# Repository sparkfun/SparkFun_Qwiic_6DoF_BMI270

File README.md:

SparkFun Qwiic 6DoF BMI270
========================================

<table class="table table-hover table-striped table-bordered">
    <tr align="center">
        <td></td>
        <td></td>
    </tr>
    <tr align="center">
        <td><i><a href="https://www.sparkfun.com/products/22397">SparkFun 6DoF IMU Breakout - BMI270 (Qwiic)</a></td></i></td>
        <td><i><a href="https://www.sparkfun.com/products/22398">SparkFun Micro 6DoF IMU Breakout - BMI270 (Qwiic)</a></i></td>
    </tr>
</table>

The SparkFun BMI270 6DoF IMU Breakout is a Qwiic-enabled breakout board based on the ultra-low power BMI270 from Bosch. This chip is a highly integrated, low power IMU optimized for wearables providing precise acceleration, angular rate measurement and intelligent on-chip motion-triggered interrupt features.. Not only does the BMI270 comprise a fast and sensitive accelerometer and gyro pair, but it also contains a number of intelligent, on-chip motion-triggered interrupt features.  

Our Standard-sized 1in. x 1in. Qwiic BMI270 IMU Breakout makes it easy to add this sensor to your project using our solderless Qwiic cables and compatible controllers. If you still prefer to use a breadboard, don't worry, we've still broken out all IO pins to 0.1" spaced pin-headers along the sides of the board. On-board solder jumpers allow you to easily select the device address, remove the I²C pull-ups, and disable the power LED if need be. 

Our Micro-sized 0.3in. x 0.75in. footprint makes this breakout board an ideal option for your smallest projects using our solderless Qwiic cables and compatible controllers. On-board solder jumpers allow you to easily select the device address, remove the I²C pull-ups, and disable the power LED if need be. 

The 6-axis sensor combines a 16-bit tri-axial gyroscope and a 16-bit tri-axial accelerometer featuring Bosch’s automotive-proven gyroscope technology. BMI270 includes several functionalities such as an integrated plug-and-play step counter/detector and gesture detection for wrist-worn devices. Moreover, the IMU is suitable for hearables, smart clothes, smart shoes, smart glasses and ankle bands.

Repository Contents
-------------------

* **/Documentation** - Data sheets, additional product information
* **/Hardware** - Eagle design files (.brd, .sch)
* **/Production** - Production panel files (.brd)

Documentation
--------------
* **[Library](https://github.com/sparkfun/SparkFun_BMI270_Arduino_Library)** - Arduino library for the SparkFun 6DoF IMU Breakout - BMI270 (Qwiic) and SparkFun Micro 6DoF IMU Breakout - BMI270 (Qwiic).
* **[Hookup Guide](http://docs.sparkfun.com/SparkFun_Qwiic_6DoF_BMI270/)** - Basic hookup guide for the SparkFun 6DoF IMU Breakout - BMI270 (Qwiic) and SparkFun Micro 6DoF IMU Breakout - BMI270 (Qwiic). 

License Information
-------------------

This product is _**open source**_! 

Please review the LICENSE.md file for license information. 

If you have any questions or concerns on licensing, please contact technical support on our [SparkFun forums](https://forum.sparkfun.com/viewforum.php?f=152).

Distributed as-is; no warranty is given.

- Your friends at SparkFun.

_<COLLABORATION CREDIT>_

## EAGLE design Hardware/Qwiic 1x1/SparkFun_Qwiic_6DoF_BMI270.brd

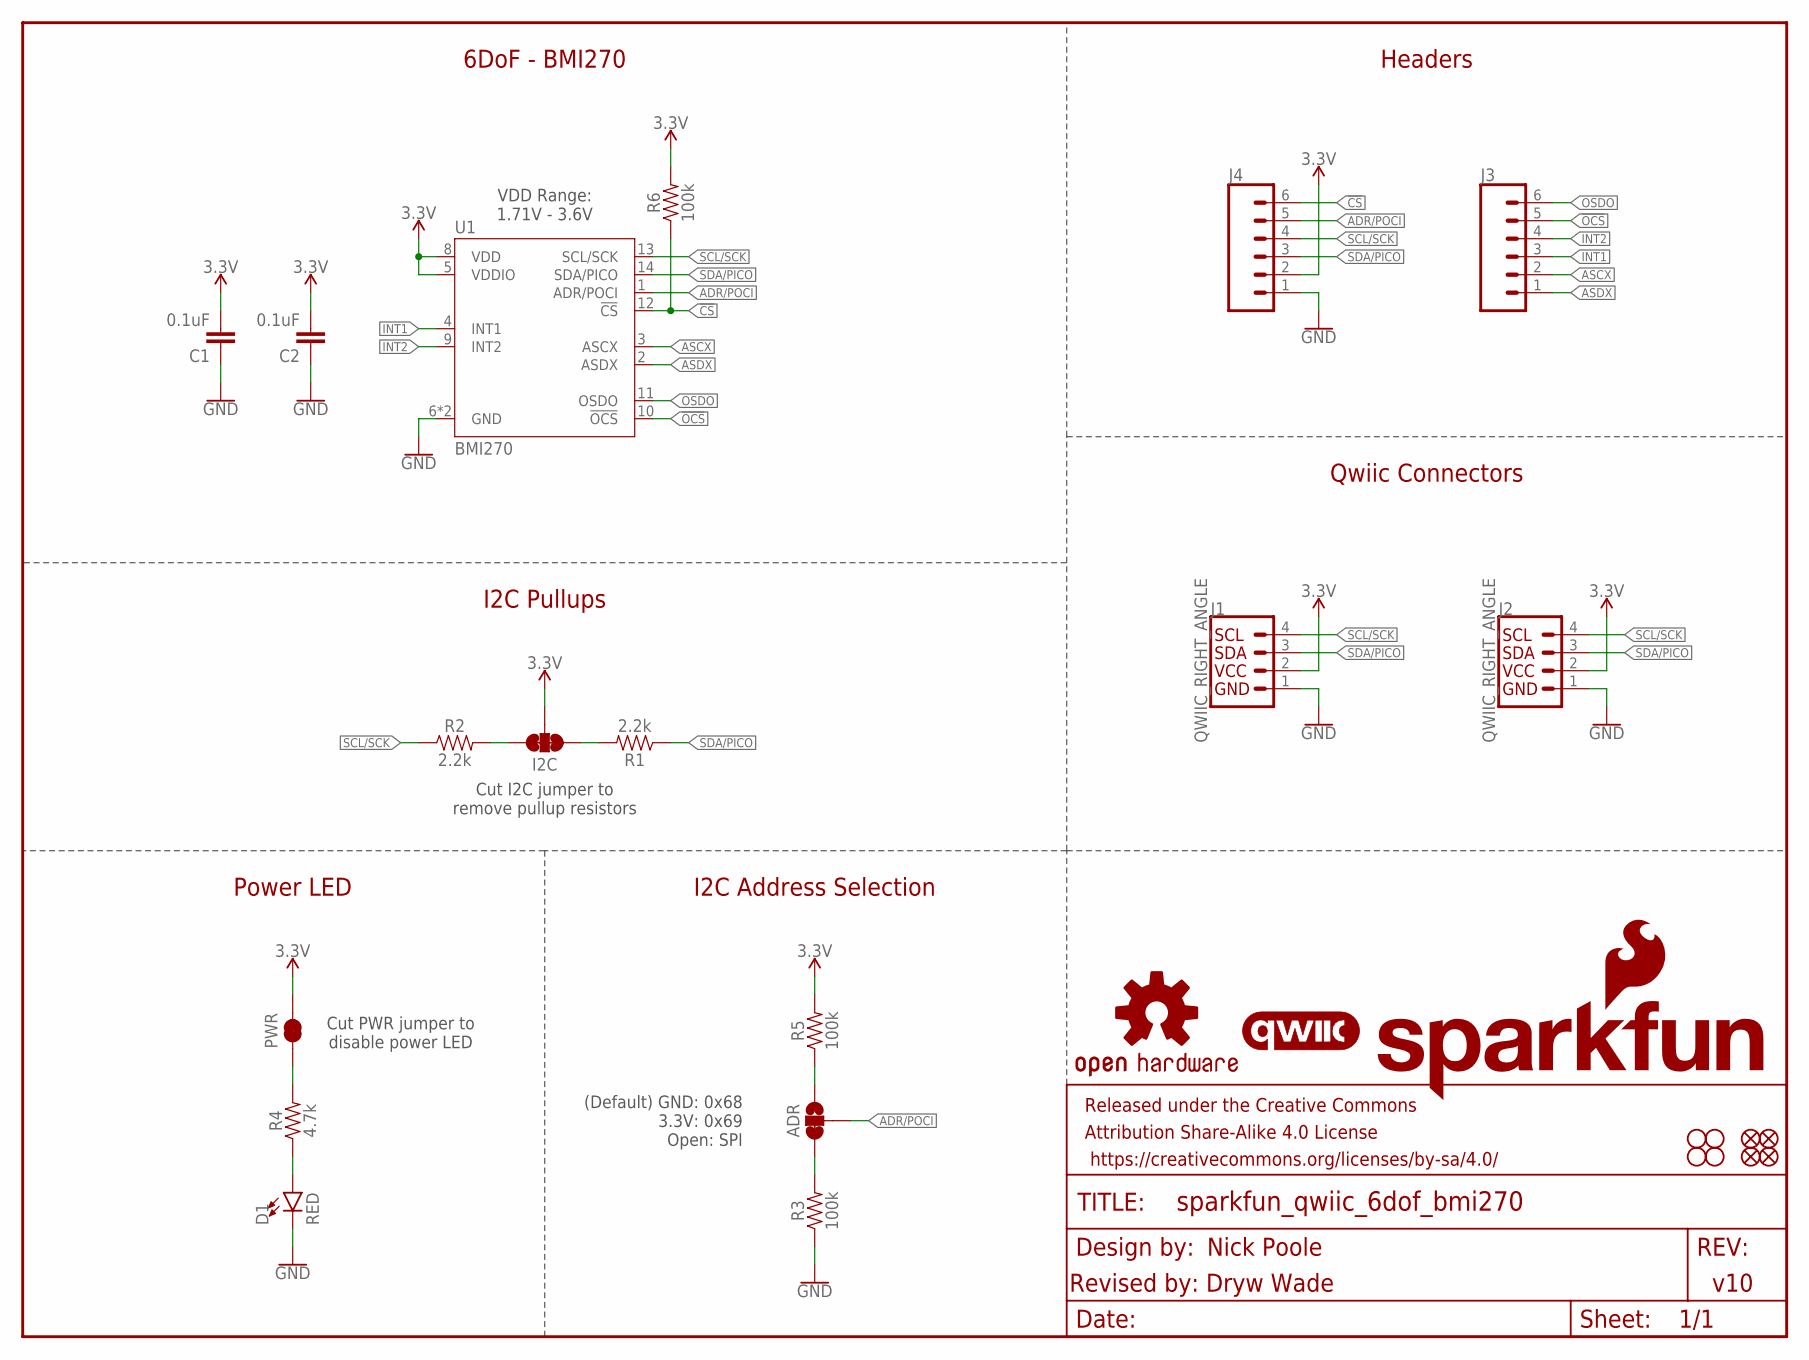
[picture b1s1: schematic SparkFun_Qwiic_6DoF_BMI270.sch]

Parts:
ADR: JUMPER-SMT_3_1-NC_TRACE_SILK; SMT-JUMPER_3_1-NC_TRACE_SILK
C1, C2: 0.1uF; 0603
D1: RED; LED-0603
FD1, FD2, FD3, FD4: FIDUCIAL1X2; FIDUCIAL-1X2
FRAME1: FRAME-LETTER; CREATIVE_COMMONS
H1, H2, H3, H4: STAND-OFF
I2C: JUMPER-SMT_3_2-NC_TRACE_SILK; SMT-JUMPER_3_2-NC_TRACE_SILK
J1, J2: QWIIC_RIGHT_ANGLE; JST04_1MM_RA
J3, J4: CONN_06NO_SILK_FEMALE_PTH; 1X06_NO_SILK
LOGO1: SFE_LOGO_NAME_FLAME.1_INCH; SFE_LOGO_NAME_FLAME_.1
LOGO2: QWIIC_LOGO_5MM; QWIIC_5MM
LOGO3: OSHW-LOGOS; OSHW-LOGO-S
PWR: JUMPER-SMT_2_NC_TRACE_SILK; SMT-JUMPER_2_NC_TRACE_SILK
R1, R2: 2.2k; 0603
R3, R5, R6: 100k; 0603
R4: 4.7k; 0603
U1: BMI270

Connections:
3.3V: C1.2, C2.2, I2C.2, J1.2, J2.2, J4.2, PWR.2, R5.2, R6.2, U1.5 (VDDIO), U1.8 (VDD)
!CS!: J4.6, R6.1, U1.12 (!CS!)
!OCS!: J3.5, U1.10 (!OCS!)
ADR/POCI: ADR.2, J4.5, U1.1 (ADR/POCI)
ASCX: J3.2, U1.3 (ASCX)
ASDX: J3.1, U1.2 (ASDX)
GND: C1.1, C2.1, D1.C, J1.1, J2.1, J4.1, R3.1, U1.6 (GND), U1.7 (GND)
INT1: J3.3, U1.4 (INT1)
INT2: J3.4, U1.9 (INT2)
unnamed: I2C.1, R1.2
unnamed: I2C.3, R2.2
unnamed: PWR.1, R4.2
unnamed: D1.A, R4.1
unnamed: ADR.1, R5.1
unnamed: ADR.3, R3.2
OSDO: J3.6, U1.11 (OSDO)
SCL/SCK: J1.4, J2.4, J4.4, R2.1, U1.13 (SCL/SCK)
SDA/PICO: J1.3, J2.3, J4.3, R1.1, U1.14 (SDA/PICO)

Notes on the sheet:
(Default) GND: 0x68 3.3V: 0x69 Open: SPI
Cut PWR jumper to disable power LED
Power LED
Headers
Qwiic Connectors
Nick Poole
Revised by: Dryw Wade
v10
6DoF - BMI270
Cut I2C jumper to remove pullup resistors
VDD Range: 1.71V - 3.6V
I2C Address Selection
I2C Pullups

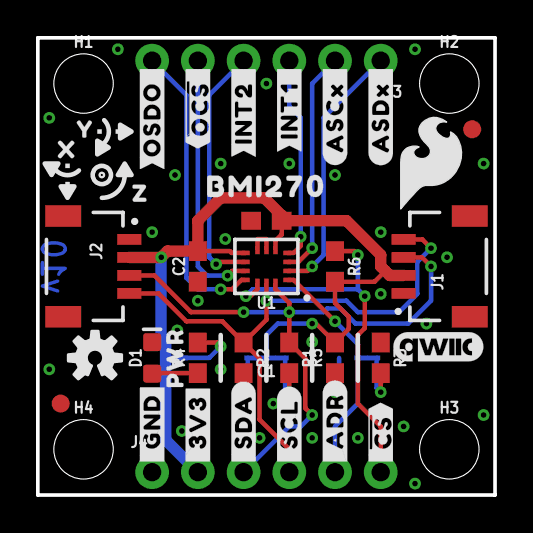
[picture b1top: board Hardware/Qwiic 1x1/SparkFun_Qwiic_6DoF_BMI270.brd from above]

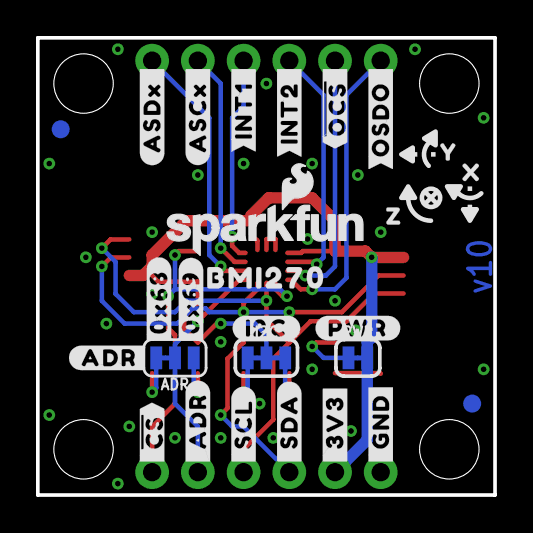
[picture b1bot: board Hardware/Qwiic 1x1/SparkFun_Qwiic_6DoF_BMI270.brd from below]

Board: 2 copper layers, 25.4 x 25.4 mm, 69 parts (27 on the bottom side), 18 nets.

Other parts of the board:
U$1: #I2C#0
U$2, U$14: #_SDA#0
U$3: SFE_LOGO_FLAME_.2
U$4: #PWR#0
U$5: #ADR#0
U$6: #0X68#0
U$7, U$13: #_3V3#0
U$8, U$17: #_#CS##0
U$9, U$16: #_ADR#0
U$10, U$15: #_SCL#0
U$11, U$27: #ASDX_#0
U$12, U$19: #_GND#0
U$18: #0X69#0
U$20, U$21: BMI2700
U$22, U$28: #ASCX_#0
U$23, U$29: #INT1_#0
U$24, U$30: #INT2_#0
U$25, U$31: ##OCS#_#0
U$26, U$32: #OSDO_#0
U$33: ORDERING_INSTRUCTIONS
U$34: PWR0
U$79, U$88: X0
U$80, U$89: Y0
U$81, U$90: Z0

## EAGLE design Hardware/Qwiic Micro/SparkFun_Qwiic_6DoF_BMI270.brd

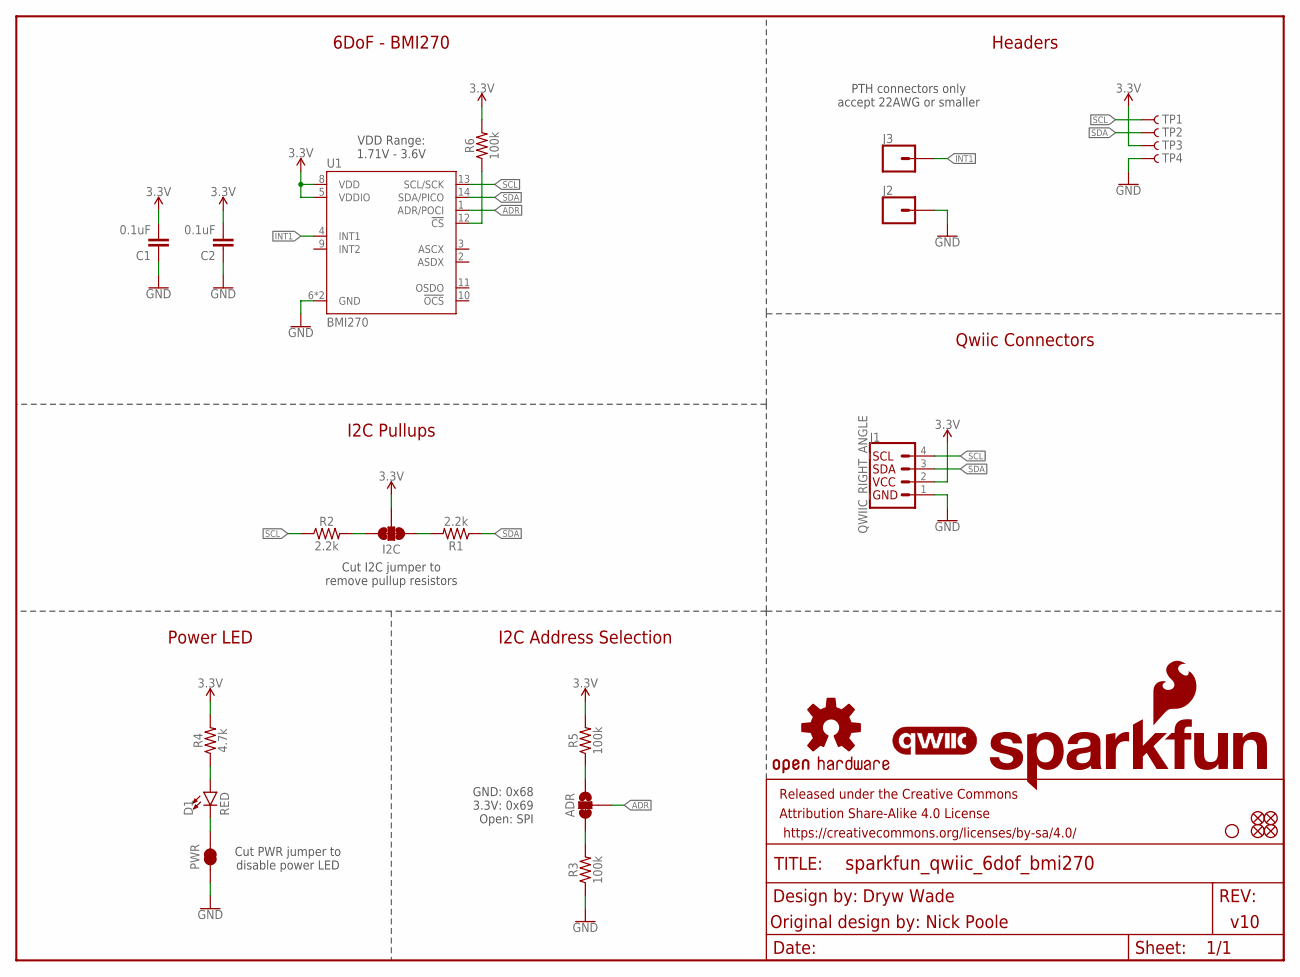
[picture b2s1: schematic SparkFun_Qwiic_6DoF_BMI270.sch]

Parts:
ADR: JUMPER-SMT_3_1-NC_TRACE_SILK; SMT-JUMPER_3_1-NC_TRACE_SILK
C1, C2: 0.1uF; 0402-TIGHT
D1: RED; LED-0402
FD1, FD2, FD3, FD4: FIDUCIALUFIDUCIAL; FIDUCIAL-MICRO
FRAME1: FRAME-LETTER; CREATIVE_COMMONS
H1: STAND-OFF
I2C: JUMPER-SMT_3_2-NC_TRACE_SILK; SMT-JUMPER_3_2-NC_TRACE_SILK
J1: QWIIC_RIGHT_ANGLE; JST04_1MM_RA
J2, J3: CONN_01_1MM; 1X01_1MM_NO_SILK
LOGO1: SFE_LOGO_NAME_FLAMEBLANK; BLANK
LOGO2: QWIIC_LOGO_3MM; QWIIC_3MM
LOGO3: OSHW-LOGOMINI; OSHW-LOGO-MINI
PWR: JUMPER-SMT_2_NC_TRACE_SILK; SMT-JUMPER_2_NC_TRACE_SILK
R1, R2: 2.2k; 0402-TIGHT
R3, R5, R6: 100k; 0402-TIGHT
R4: 4.7k; 0402-TIGHT
TP1, TP2, TP3, TP4: TEST-POINT3; PAD.03X.03
U1: BMI270

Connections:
3.3V: C1.2, C2.2, I2C.2, J1.2, R4.2, R5.2, R6.2, TP3.1, U1.5 (VDDIO), U1.8 (VDD)
ADR: ADR.2, U1.1 (ADR/POCI)
GND: C1.1, C2.1, J1.1, J2.1, PWR.1, R3.1, TP4.1, U1.6 (GND), U1.7 (GND)
INT1: J3.1, U1.4 (INT1)
unnamed: I2C.1, R1.2
unnamed: I2C.3, R2.2
unnamed: D1.C, PWR.2
unnamed: D1.A, R4.1
unnamed: ADR.1, R5.1
unnamed: ADR.3, R3.2
unnamed: R6.1, U1.12 (!CS!)
SCL: J1.4, R2.1, TP1.1, U1.13 (SCL/SCK)
SDA: J1.3, R1.1, TP2.1, U1.14 (SDA/PICO)

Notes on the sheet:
GND: 0x68 3.3V: 0x69 Open: SPI
Cut PWR jumper to disable power LED
Power LED
Headers
Qwiic Connectors
Dryw Wade
Original design by: Nick Poole
v10
6DoF - BMI270
Cut I2C jumper to remove pullup resistors
VDD Range: 1.71V - 3.6V
I2C Address Selection
I2C Pullups
PTH connectors only accept 22AWG or smaller

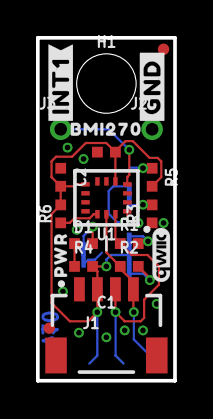
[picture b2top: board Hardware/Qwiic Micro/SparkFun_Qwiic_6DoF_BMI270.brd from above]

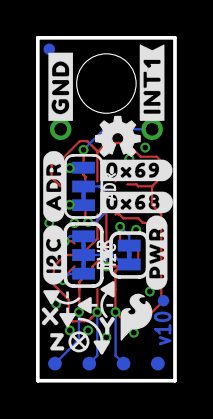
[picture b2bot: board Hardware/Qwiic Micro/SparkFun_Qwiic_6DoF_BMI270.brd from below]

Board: 2 copper layers, 7.6 x 19.1 mm, 45 parts (22 on the bottom side), 13 nets.

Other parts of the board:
U$1: #I2C#0
U$2, U$7: #GND#0
U$3: SFE_LOGO_FLAME_.1
U$4: #PWR#0
U$5: #ADR#0
U$6: #0X68#0
U$8, U$9: #INT1#0
U$18: #0X69#0
U$21: BMI2700
U$33: ORDERING_INSTRUCTIONS
U$34: PWR0
U$79: X0
U$80: Y0
U$81: Z0

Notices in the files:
parts and their libraries:
SparkFun-LED: Licensing: Creative Commons ShareAlike 4.0 International - https://creativecommons.org/licenses/by-sa/4.0
SparkFun-Aesthetics: Released under the Creative Commons Attribution Share-Alike 4.0 License
SparkFun-Aesthetics: https://creativecommons.org/licenses/by-sa/4.0
